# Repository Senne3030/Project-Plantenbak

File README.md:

Project plantenbak

Met dit project willen we ons leven makkelijker maken, om zo planten te kweken terwijl we weinig moeite te doen.

Om te starten met dit project download je de codes, waarwan je de C++ code nodig hebt op je ESP32 en de python code nodig hebt op de raspberry pi.
Vervolgens download je de documentatie zodat je alles van dit project weet en het zelf kan nabouwen. Veel plezier!

GerberFilePlantenbak.zip heb je nodig om dit te laten maken, maar ik raad aan de documentatie te lezen, van mijn fouten te leren en dan je eigen PCB te maken.
Plantenbak-v3.brd is de PCB.
Plantenbak-v3.sch is het schema.
Main.cpp is de C++ code, voor op je ESP32. (Ik gebruik Visual Studio Code om deze code te maken.)
pythonMQTT1.py is de python code, voor je raspberry pi. Als je deze naam hetzelfde houd dan moet je er op letten dat je deze naam ook ingeeft als je een systemctl service (automatisch opstarten) maakt.
"Documentatie Project Plantenbak" is de documentatie, daar staat alles in dat je moet weten.

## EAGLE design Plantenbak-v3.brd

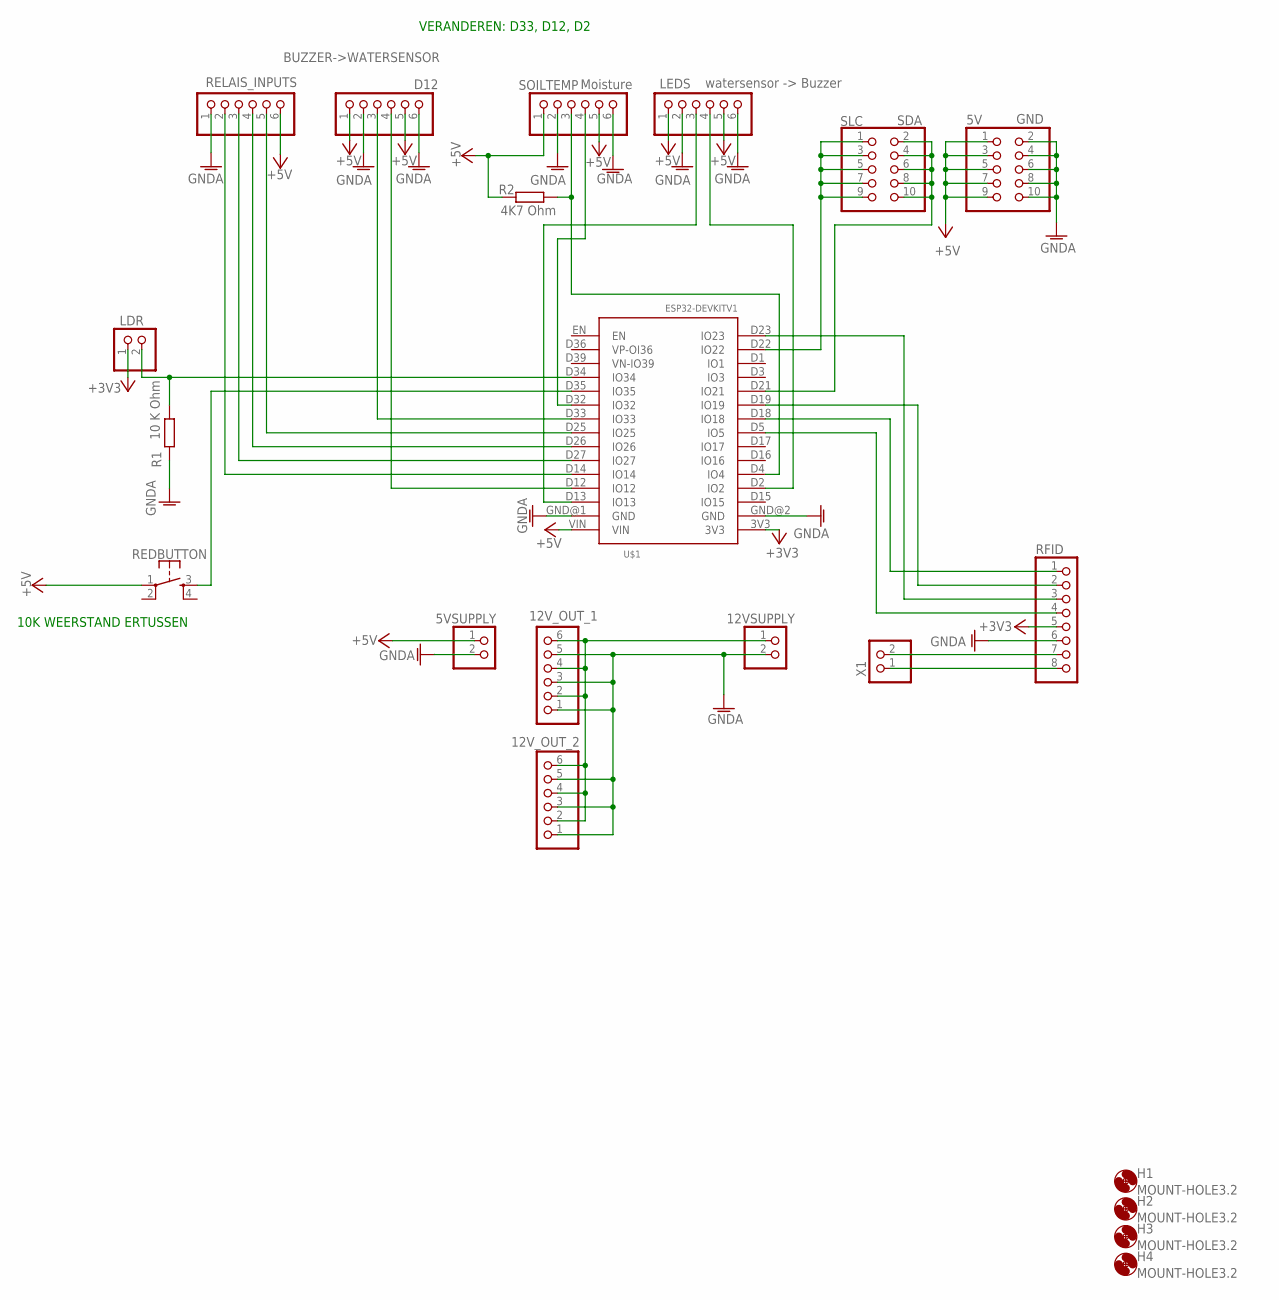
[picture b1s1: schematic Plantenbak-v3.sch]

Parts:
5V: GND; 2X05
5VSUPPLY, 12VSUPPLY: PINHD-1X2; 1X02
12V_OUT_1, 12V_OUT_2: PINHD-1X6; 1X06
BUZZER->WATERSENSOR: D12; 1X06
H1, H2, H3, H4: MOUNT-HOLE3.2; 3,2
LDR: PINHD-1X2; 1X02
LEDS: watersensor -> Buzzer; 1X06
R1: 10 K Ohm; 0204/7
R2: 4K7 Ohm; 0204/7
REDBUTTON: MOMENTARY-SWITCH-SPST-2-SMD-5.2MM; TACTILE_SWITCH_SMD_5.2MM
RELAIS_INPUTS: PINHD-1X6; 1X06
RFID: PINHD-1X8; 1X08
SLC: SDA; 2X05
SOILTEMP: Moisture; 1X06
U$1: ESP32DEVKITV1; ESP32-DEVKITV1
X1: PINHD-1X2; 1X02

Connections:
+3V3: LDR.1, RFID.5, U$1.3V3
+5V: 5V.1, 5V.3, 5V.5, 5V.7, 5V.9, 5VSUPPLY.1, BUZZER->WATERSENSOR.1, BUZZER->WATERSENSOR.5, LEDS.1, LEDS.5, R2.2, REDBUTTON.1, RELAIS_INPUTS.6, SOILTEMP.1, SOILTEMP.5, U$1.VIN
GNDA: 5V.2, 5V.4, 5V.6, 5V.8, 5V.10, 5VSUPPLY.2, 12VSUPPLY.2, 12V_OUT_1.1, 12V_OUT_1.3, 12V_OUT_1.5, 12V_OUT_2.1, 12V_OUT_2.3, 12V_OUT_2.5, BUZZER->WATERSENSOR.2, BUZZER->WATERSENSOR.6, LEDS.2, LEDS.6, R1.1, RELAIS_INPUTS.1, RFID.6, SOILTEMP.2, SOILTEMP.6, U$1.GND@1 (GND), U$1.GND@2 (GND)
unnamed: SLC.1, SLC.3, SLC.5, SLC.7, SLC.9, U$1.D22 (IO22)
unnamed: LEDS.3, U$1.D13 (IO13)
unnamed: SLC.2, SLC.4, SLC.6, SLC.8, SLC.10, U$1.D21 (IO21)
unnamed: SOILTEMP.4, U$1.D32 (IO32)
unnamed: LDR.2, R1.2, U$1.D34 (IO34)
unnamed: RFID.2, U$1.D19 (IO19)
unnamed: RFID.3, U$1.D23 (IO23)
unnamed: RFID.1, U$1.D18 (IO18)
unnamed: RFID.4, U$1.D5 (IO5)
unnamed: LEDS.4, U$1.D2 (IO2)
unnamed: R2.1, SOILTEMP.3, U$1.D4 (IO4)
unnamed: RFID.7, X1.2
unnamed: RFID.8, X1.1
unnamed: RELAIS_INPUTS.2, U$1.D14 (IO14)
unnamed: RELAIS_INPUTS.3, U$1.D27 (IO27)
unnamed: BUZZER->WATERSENSOR.3, U$1.D33 (IO33)
unnamed: BUZZER->WATERSENSOR.4, U$1.D12 (IO12)
unnamed: REDBUTTON.3, U$1.D35 (IO35)
unnamed: RELAIS_INPUTS.4, U$1.D26 (IO26)
unnamed: RELAIS_INPUTS.5, U$1.D25 (IO25)
unnamed: 12VSUPPLY.1, 12V_OUT_1.2, 12V_OUT_1.4, 12V_OUT_1.6, 12V_OUT_2.2, 12V_OUT_2.4, 12V_OUT_2.6

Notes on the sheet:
VERANDEREN: D33, D12, D2
10K WEERSTAND ERTUSSEN

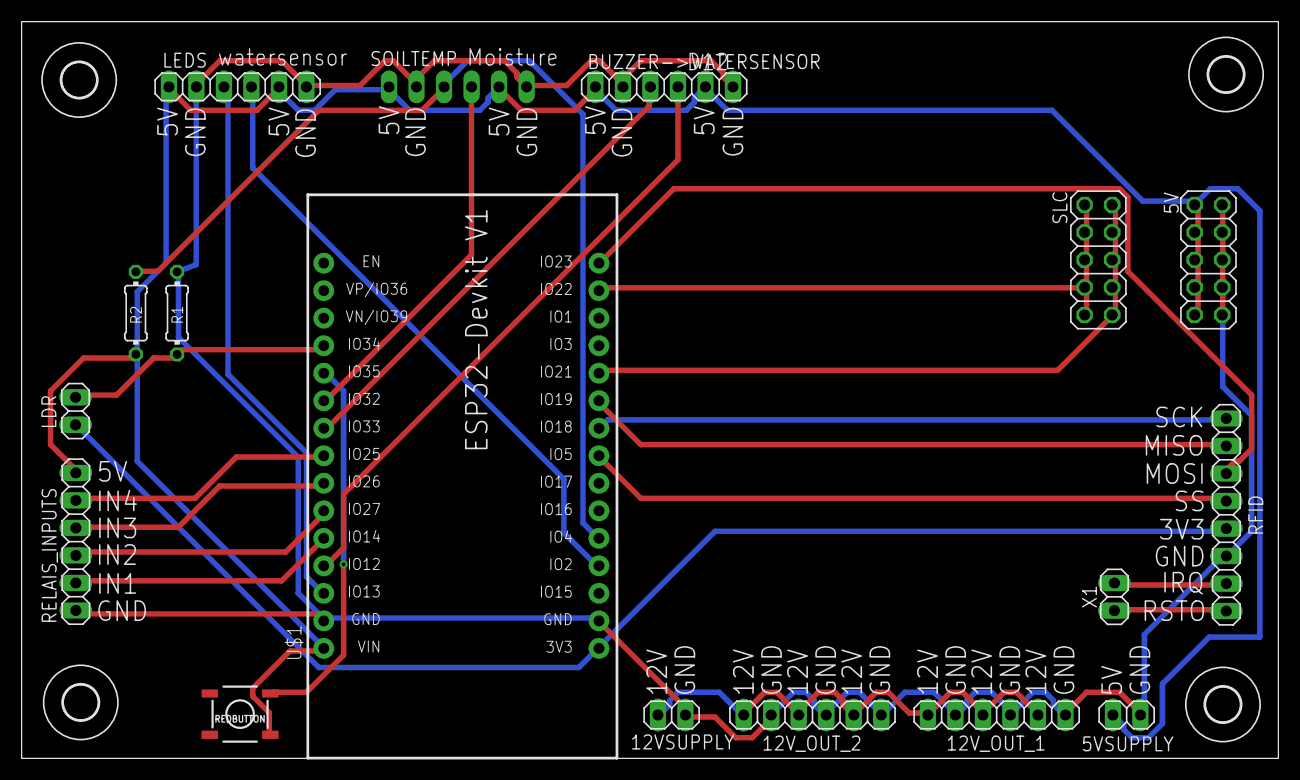
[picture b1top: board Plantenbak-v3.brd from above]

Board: 2 copper layers, 116.0 x 68.0 mm, 21 parts (1 on the bottom side), 24 nets.

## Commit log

2024-06-11 pythonMQTT1.py

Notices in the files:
parts and their libraries:
SparkFun-Switches: Licensing: Creative Commons ShareAlike 4.0 International - https://creativecommons.org/licenses/by-sa/4.0
